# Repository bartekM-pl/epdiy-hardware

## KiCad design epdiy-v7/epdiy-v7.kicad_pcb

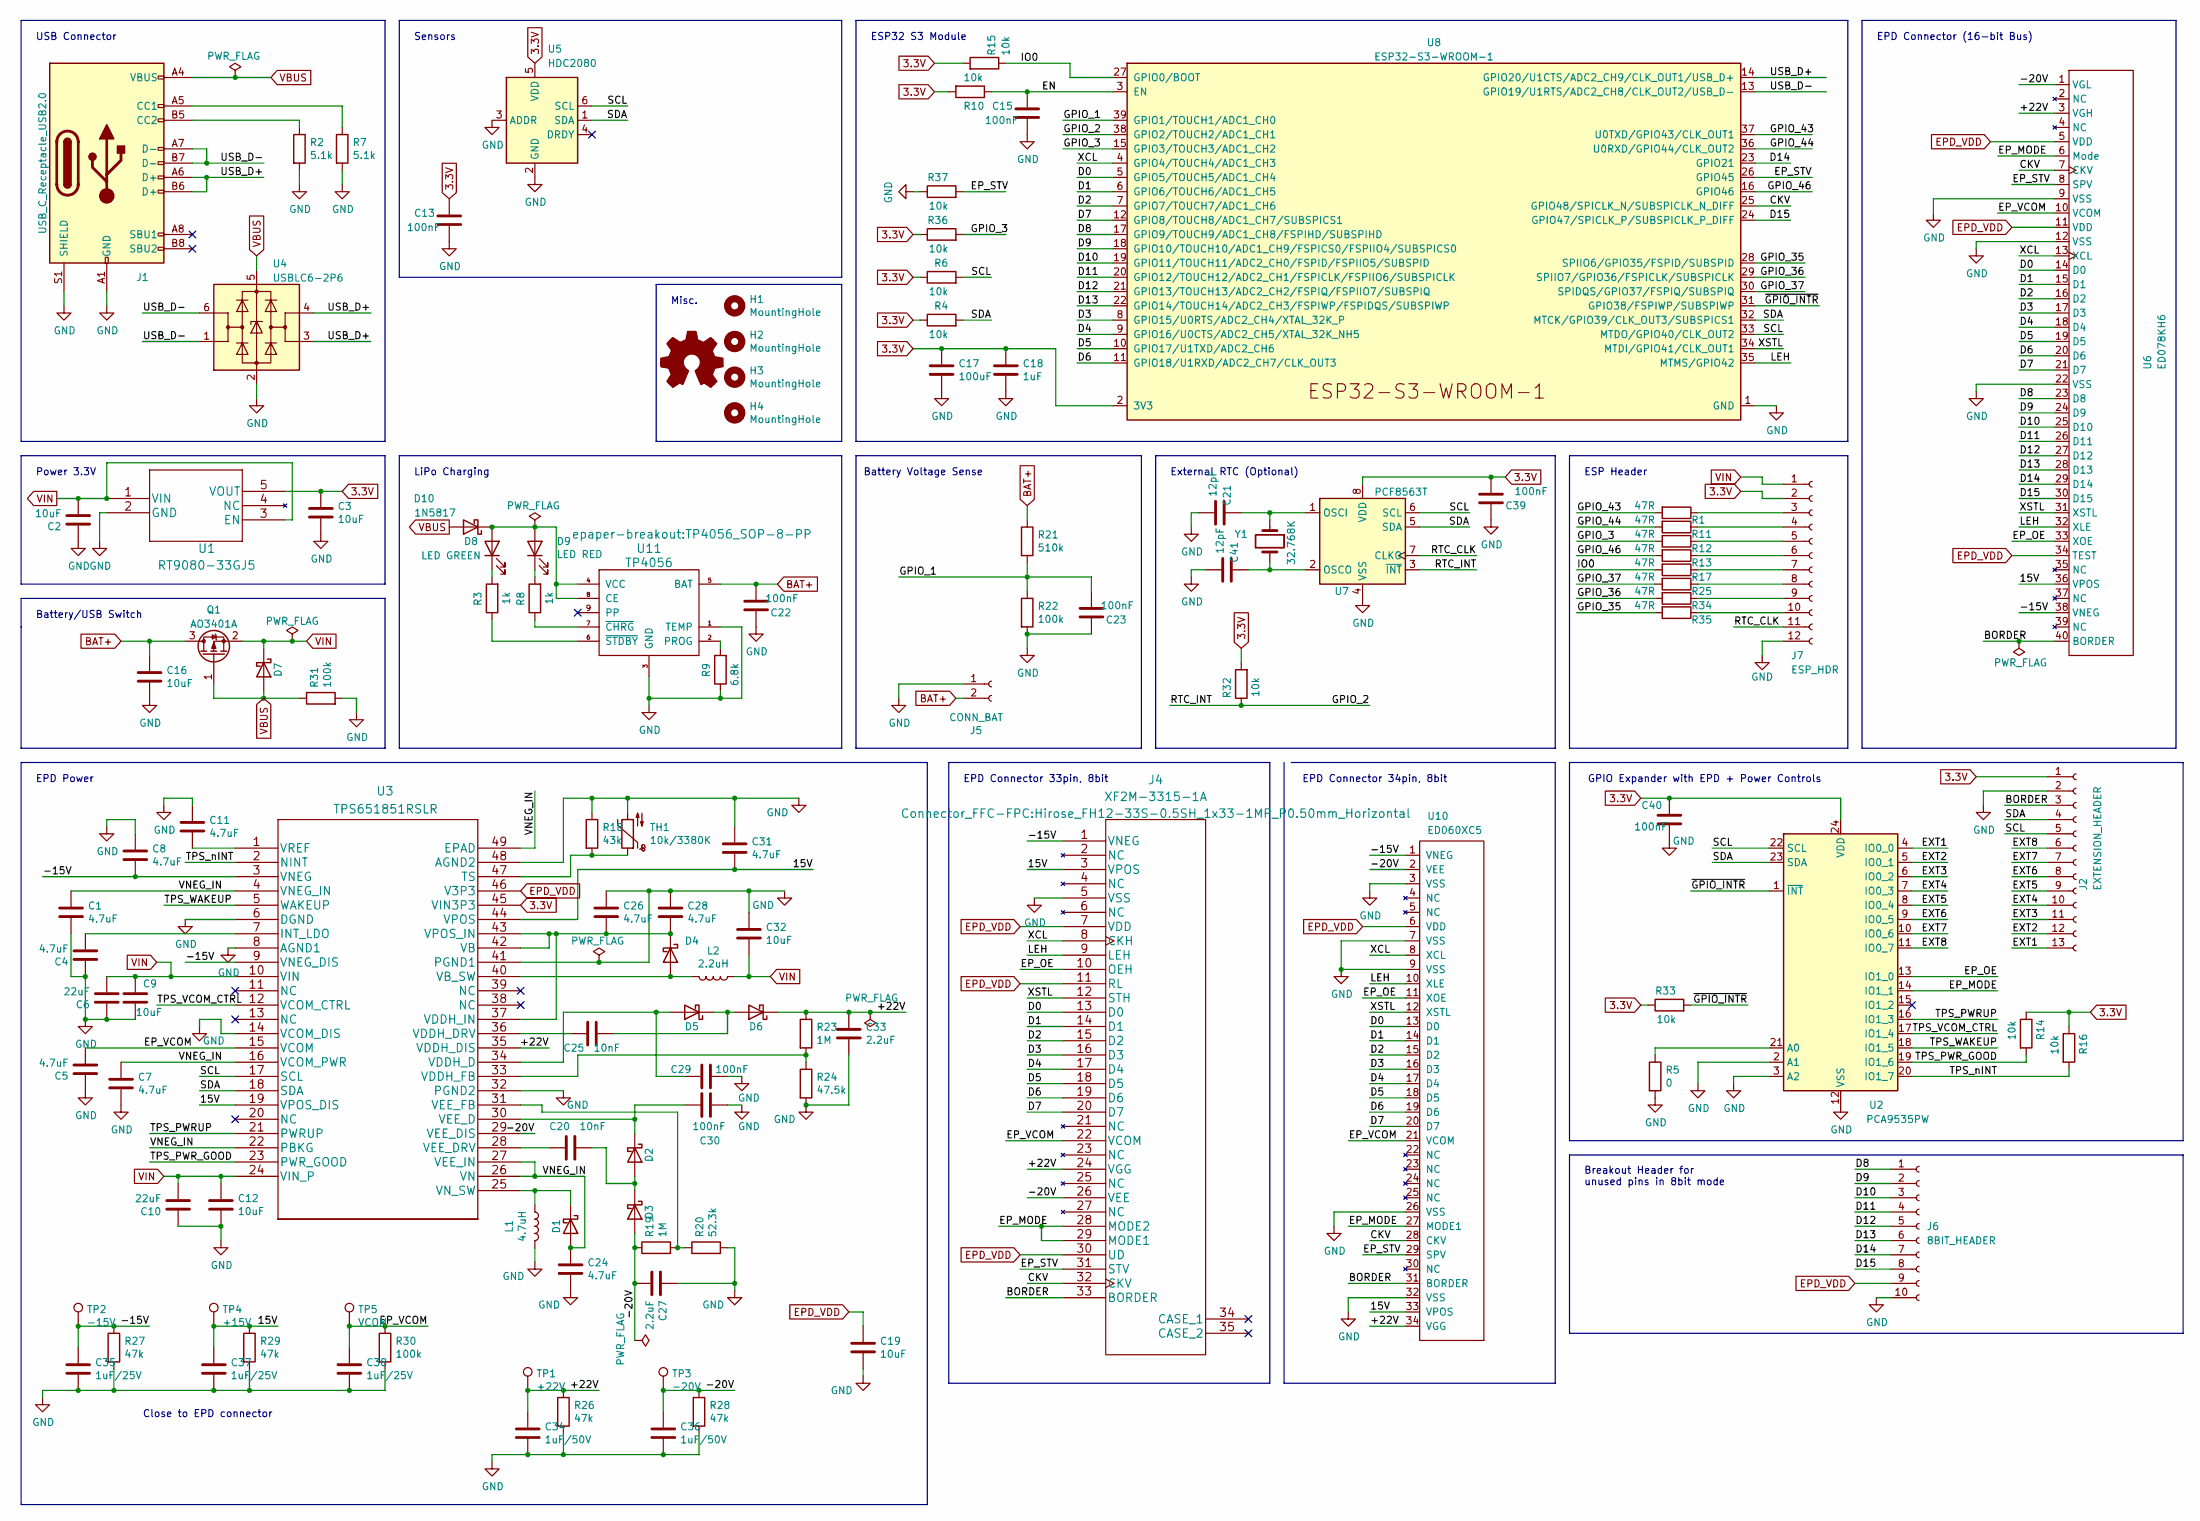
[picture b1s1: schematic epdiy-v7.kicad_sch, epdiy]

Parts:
C1, C4, C5, C7, C8, C11, C24, C26, C28, C31: 4.7uF; C_0805_2012Metric; LCSC C1779
C2, C3, C9, C12, C16, C19, C32: 10uF; C_0805_2012Metric; LCSC C15850
C6, C10: 22uF; C_0805_2012Metric; LCSC C45783
C13: 100nF; C_0603_1608Metric; LCSC C49678
C15, C22, C23, C29, C30, C39, C40: 100nF; C_0805_2012Metric; LCSC C49678
C17: 100uF; CP_EIA-3528-15_AVX-H; LCSC C16133
C18: 1uF; C_0805_2012Metric; LCSC C28323
C20, C25: 10nF; C_0805_2012Metric; LCSC C1710
C21, C41: 12pF; C_0603_1608Metric; LCSC C38523
C27, C33: 2.2uF; C_0805_2012Metric; LCSC C377773
C34, C36: 1uF/50V; C_1206_3216Metric; LCSC C1848
C35, C37, C38: 1uF/25V; C_0805_2012Metric; LCSC C28323
D1, D2, D3, D4, D5, D6, D7: MBR0540; D_SOD-123; LCSC C8598
D8: LED GREEN; LED_0603_1608Metric; LCSC C72043
D9: LED RED; LED_0603_1608Metric; LCSC C72038
D10: 1N5817; D_SOD-123; LCSC C8598
H1, H2, H3, H4: MountingHole; MountingHole_2.2mm_M2
J1: USB_C_Receptacle_USB2.0; USB_C_Receptacle_HRO_TYPE-C-31-M-12; LCSC C165948
J2: EXTENSION_HEADER; PinHeader_1x13_P2.54mm_Vertical
J4: XF2M-3315-1A; Hirose_FH12-33S-0.5SH_1x33-1MP_P0.50mm_Horizontal; LCSC C597986
J5: CONN_BAT; PinHeader_1x02_P2.54mm_Vertical
J6: 8BIT_HEADER; PinHeader_1x10_P2.54mm_Vertical
J7: ESP_HDR; PinHeader_1x12_P2.54mm_Vertical
L1: 4.7uH; L_Taiyo-Yuden_NR-50xx_HandSoldering; LCSC C222947
L2: 2.2uH; L_Taiyo-Yuden_NR-40xx_HandSoldering; LCSC C92959
Q1: AO3401A; SOT-23; LCSC C15127
R1, R11, R12, R13, R17, R25, R34, R35: 47R; R_0603_1608Metric; LCSC C25804
R2, R7: 5.1k; R_0603_1608Metric; LCSC C23186
R3, R8: 1k; R_0603_1608Metric; LCSC C21190
R4, R6, R10, R14, R15, R16, R32, R33, R36, R37: 10k; R_0603_1608Metric; LCSC C25804
R5: 0; R_0603_1608Metric; LCSC C21189
R9: 6.8k; R_0603_1608Metric; LCSC C23212
R18: 43k; R_0603_1608Metric; LCSC C23172
R19, R23: 1M; R_0603_1608Metric; LCSC C22935
R20: 52.3k; R_0603_1608Metric; LCSC C23196
R21: 510k; R_0603_1608Metric; LCSC C23192
R22: 100k; R_0603_1608Metric; LCSC C22807
R24: 47.5k; R_0603_1608Metric; LCSC C25819
R26, R27, R28, R29: 47k; R_0603_1608Metric; LCSC C25819
R30, R31: 100k; R_0603_1608Metric; LCSC C25803
TH1: 10k/3380K; R_0603_1608Metric; LCSC C76589
TP1: +22V; TestPoint_Pad_D2.5mm
TP2: -15V; TestPoint_Pad_D2.5mm
TP3: -20V; TestPoint_Pad_D2.5mm
TP4: +15V; TestPoint_Pad_D2.5mm
TP5: VCOM; TestPoint_Pad_D2.5mm
U1: RT9080-33GJ5; TSOT-23-5; LCSC C841192
U2: PCA9535PW; TSSOP-24_4.4x7.8mm_P0.65mm; LCSC C2652292
U3: TPS651851RSLR; LCSC C139292
U4: USBLC6-2P6; SOT-666; LCSC C2827693
U5: HDC2080; Texas_PWSON-N6; LCSC C918141
U6: ED078KH6; Hirose_FH12-40S-0.5SH_1x40-1MP_P0.50mm_Horizontal; LCSC C202114
U7: PCF8563T; SOIC-8_3.9x4.9mm_P1.27mm; LCSC C7440
U8: ESP32-S3-WROOM-1; LCSC C2913202
U10: ED060XC5; X05A20H34G; LCSC C528053
U11: TP4056; TP4056_SOP-8-PP; LCSC C16581
Y1: 32.768K; Crystal_SMD_3215-2Pin_3.2x1.5mm; LCSC C32346

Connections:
3.3V: C3.2, C13.1, C17.1, C18.2, C39.2, C40.1, J2.1, J7.2, R4.1, R6.1, R10.2, R14.1, R15.2, R16.1, R32.2, R33.1, R36.1, U1.5 (VOUT), U2.24 (VDD), U3.45 (VIN3P3), U5.5 (VDD), U7.8 (VDD), U8.2 (3V3)
/15V: C31.2, C37.1, J4.3 (VPOS), R29.1, TP4.1, U3.19 (VPOS_DIS), U3.44 (VPOS), U6.36 (VPOS), U10.33 (VPOS)
/+22V: C33.1, C34.1, D6.1 (K), J4.24 (VGG), R23.1, R26.1, TP1.1, U3.35 (VDDH_DIS), U6.3 (VGH), U10.34 (VGG)
/-15V: C8.2, C35.1, J4.1 (VNEG), R27.1, TP2.1, U3.3 (VNEG), U3.9 (VNEG_DIS), U6.38 (VNEG), U10.1 (VNEG)
/-20V: C27.2, C36.1, D3.2 (A), J4.26 (VEE), R19.1, R28.1, TP3.1, U3.29 (VEE_DIS), U6.1 (VGL), U10.2 (VEE)
/CKV: J4.32 (CKV), U6.7 (CKV), U8.25 (GPIO48/SPICLK_N/SUBSPICLK_N_DIFF), U10.28 (CKV)
/D0: J4.13 (D0), U6.14 (D0), U8.5 (GPIO5/TOUCH5/ADC1_CH4), U10.13 (D0)
/D1: J4.14 (D1), U6.15 (D1), U8.6 (GPIO6/TOUCH6/ADC1_CH5), U10.14 (D1)
/D2: J4.15 (D2), U6.16 (D2), U8.7 (GPIO7/TOUCH7/ADC1_CH6), U10.15 (D2)
/D3: J4.16 (D3), U6.17 (D3), U8.8 (GPIO15/U0RTS/ADC2_CH4/XTAL_32K_P), U10.16 (D3)
/D4: J4.17 (D4), U6.18 (D4), U8.9 (GPIO16/U0CTS/ADC2_CH5/XTAL_32K_NH5), U10.17 (D4)
/D5: J4.18 (D5), U6.19 (D5), U8.10 (GPIO17/U1TXD/ADC2_CH6), U10.18 (D5)
/D6: J4.19 (D6), U6.20 (D6), U8.11 (GPIO18/U1RXD/ADC2_CH7/CLK_OUT3), U10.19 (D6)
/D7: J4.20 (D7), U6.21 (D7), U8.12 (GPIO8/TOUCH8/ADC1_CH7/SUBSPICS1), U10.20 (D7)
/D8: J6.1, U6.23 (D8), U8.17 (GPIO9/TOUCH9/ADC1_CH8/FSPIHD/SUBSPIHD)
/D9: J6.2, U6.24 (D9), U8.18 (GPIO10/TOUCH10/ADC1_CH9/FSPICS0/FSPIIO4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)
/D10: J6.3, U6.25 (D10), U8.19 (GPIO11/TOUCH11/ADC2_CH0/FSPID/FSPIIO5/S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)
/D11: J6.4, U6.26 (D11), U8.20 (GPIO12/TOUCH12/ADC2_CH1/FSPICLK/FSPIIO6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)
/D12: J6.5, U6.27 (D12), U8.21 (GPIO13/TOUCH13/ADC2_CH2/FSPIQ/FSPIIO7/S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)
/D13: J6.6, U6.28 (D13), U8.22 (GPIO14/TOUCH14/ADC2_CH3/FSPIWP/FSPIDQS/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)
/D14: J6.7, U6.29 (D14), U8.23 (GPIO21)
/D15: J6.8, U6.30 (D15), U8.24 (GPIO47/SPICLK_P/SUBSPICLK_P_DIFF)
/EN: C15.1, R10.1, U8.3 (EN)
/EP_MODE: J4.28 (MODE2), J4.29 (MODE1), U2.14 (IO1_1), U6.6 (Mode), U10.27 (MODE1)
/EP_OE: J4.10 (OEH), U2.13 (IO1_0), U6.33 (XOE), U10.11 (XOE)
/EP_STV: J4.31 (STV), R37.2, U6.8 (SPV), U8.26 (GPIO45), U10.29 (SPV)
/EP_VCOM: C5.2, C38.1, J4.22 (VCOM), R30.1, TP5.1, U3.15 (VCOM), U6.10 (VCOM), U10.21 (VCOM)
/EXT1: J2.13, U2.4 (IO0_0)
/EXT2: J2.12, U2.5 (IO0_1)
/EXT3: J2.11, U2.6 (IO0_2)
/EXT4: J2.10, U2.7 (IO0_3)
/EXT5: J2.9, U2.8 (IO0_4)
/EXT6: J2.8, U2.9 (IO0_5)
/EXT7: J2.7, U2.10 (IO0_6)
/EXT8: J2.6, U2.11 (IO0_7)
/GPIO_1: C23.2, R21.2, R22.1, U8.39 (GPIO1/TOUCH1/ADC1_CH0)
/GPIO_2: R32.1, U7.3 (~INT), U8.38 (GPIO2/TOUCH2/ADC1_CH1)
/GPIO_3: R12.2, R36.2, U8.15 (GPIO3/TOUCH3/ADC1_CH2)
/GPIO_35: R35.2, U8.28 (SPIIO6/GPIO35/FSPID/SUBSPID)
/GPIO_36: R34.2, U8.29 (SPIIO7/GPIO36/FSPICLK/SUBSPICLK)
/GPIO_37: R25.2, U8.30 (SPIDQS/GPIO37/FSPIQ/SUBSPIQ)
/GPIO_43: R1.2, U8.37 (U0TXD/GPIO43/CLK_OUT1)
/GPIO_44: R11.2, U8.36 (U0RXD/GPIO44/CLK_OUT2)
/GPIO_46: R13.2, U8.16 (GPIO46)
/IO0: R15.1, R17.2, U8.27 (GPIO0/BOOT)
/LEH: J4.9 (LEH), U6.32 (XLE), U8.35 (MTMS/GPIO42), U10.10 (XLE)
/RTC_CLK: J7.11, U7.7 (CLKO)
/SCL: J2.5, R6.2, U2.22 (SCL), U3.17 (SCL), U5.6 (SCL), U7.6 (SCL), U8.33 (MTDO/GPIO40/CLK_OUT2)
/SDA: J2.4, R4.2, U2.23 (SDA), U3.18 (SDA), U5.1 (SDA), U7.5 (SDA), U8.32 (MTCK/GPIO39/CLK_OUT3/SUBSPICS1)
/TPS_PWRUP: U2.16 (IO1_3), U3.21 (PWRUP)
/TPS_PWR_GOOD: R14.2, U2.19 (IO1_6), U3.23 (PWR_GOOD)
/TPS_VCOM_CTRL: U2.17 (IO1_4), U3.12 (VCOM_CTRL)
/TPS_WAKEUP: U2.18 (IO1_5), U3.5 (WAKEUP)
/TPS_nINT: R16.2, U2.20 (IO1_7), U3.2 (NINT)
/USB_D+: J1.A6 (D+), J1.B6 (D+), U4.3 (I/O2), U4.4 (I/O2), U8.14 (GPIO20/U1CTS/ADC2_CH9/CLK_OUT1/USB_D+)
/USB_D-: J1.A7 (D-), J1.B7 (D-), U4.1 (I/O1), U4.6 (I/O1), U8.13 (GPIO19/U1RTS/ADC2_CH8/CLK_OUT2/USB_D-)
/VNEG_IN: C1.1, C7.1, C24.1, D1.2 (A), U3.4 (VNEG_IN), U3.16 (VCOM_PWR), U3.22 (PBKG), U3.26 (VN), U3.27 (VEE_IN), U3.49 (EPAD)
/XCL: J4.8 (CKH), U6.13 (XCL), U8.4 (GPIO4/TOUCH4/ADC1_CH3), U10.8 (XCL)
/XSTL: J4.12 (STH), U6.31 (XSTL), U8.34 (MTDI/GPIO41/CLK_OUT1), U10.12 (XSTL)
/~GPIO_INTR: R33.2, U2.1 (~INT), U8.31 (GPIO38/FSPIWP/SUBSPIWP)
BAT+: C16.2, C22.2, J5.2, Q1.3 (D), R21.1, U11.5 (BAT)
EPD_VDD: C19.1, J4.7 (VDD), J4.11 (RL), J4.30 (UD), J6.9, U3.46 (V3P3), U6.5 (VDD), U6.11 (VDD), U6.34 (TEST), U10.6 (VDD)
unnamed: D1.1 (K), L1.1, U3.25 (VN_SW)
unnamed: C20.1, D2.2 (A), D3.1 (K)
unnamed: C30.1, D2.1 (K), U3.30 (VEE_D)
unnamed: D4.2 (A), L2.2, U3.40 (VB_SW)
unnamed: C26.2, C28.2, D4.1 (K), U3.37 (VDDH_IN), U3.42 (VB), U3.43 (VPOS_IN)
unnamed: C29.2, D5.2 (A), U3.34 (VDDH_D)
unnamed: C25.1, D5.1 (K), D6.2 (A)
unnamed: D8.1 (K), R3.2
unnamed: D9.1 (K), R8.2
unnamed: D8.2 (A), D9.2 (A), D10.1 (K), U11.4 (VCC), U11.8 (CE)
unnamed: J1.A5 (CC1), R7.1
unnamed: J1.B5 (CC2), R2.1
unnamed: J7.3, R1.1
unnamed: J7.4, R11.1
unnamed: J7.5, R12.1
unnamed: J7.6, R13.1
unnamed: J7.7, R17.1
unnamed: J7.8, R25.1
unnamed: J7.9, R34.1
unnamed: J7.10, R35.1
unnamed: R5.1, U2.21 (A0)
unnamed: C4.2, U3.7 (INT_LDO)
unnamed: R18.2, TH1.1, U3.47 (TS)
unnamed: C25.2, U3.36 (VDDH_DRV)
unnamed: R23.2, R24.1, U3.33 (VDDH_FB)
unnamed: C20.2, U3.28 (VEE_DRV)
unnamed: R19.2, R20.1, U3.31 (VEE_FB)
unnamed: C11.2, U3.1 (VREF)
unnamed: C21.2, U7.1 (OSCI), Y1.1
unnamed: C41.2, U7.2 (OSCO), Y1.2
unnamed: R9.2, U11.2 (PROG)
unnamed: R8.1, U11.7 (~CHRG)
unnamed: R3.1, U11.6 (~STDBY)
VIN: C2.1, C6.2, C9.1, C10.2, C12.1, C32.2, D7.1 (K), J7.1, L2.1, Q1.2 (S), U1.1 (VIN), U1.3 (EN), U3.10 (VIN), U3.24 (VIN_P)

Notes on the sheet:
Battery Voltage Sense
Misc.
EPD Power
ESP Header
GPIO Expander with EPD + Power Controls
USB Connector
EPD Connector (16-bit Bus)
ESP32 S3 Module
Power 3.3V
EPD Connector 33pin, 8bit
Battery/USB Switch
External RTC (Optional)
EPD Connector 34pin, 8bit
Sensors
Breakout Header for unused pins in 8bit mode
LiPo Charging
Close to EPD connector

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
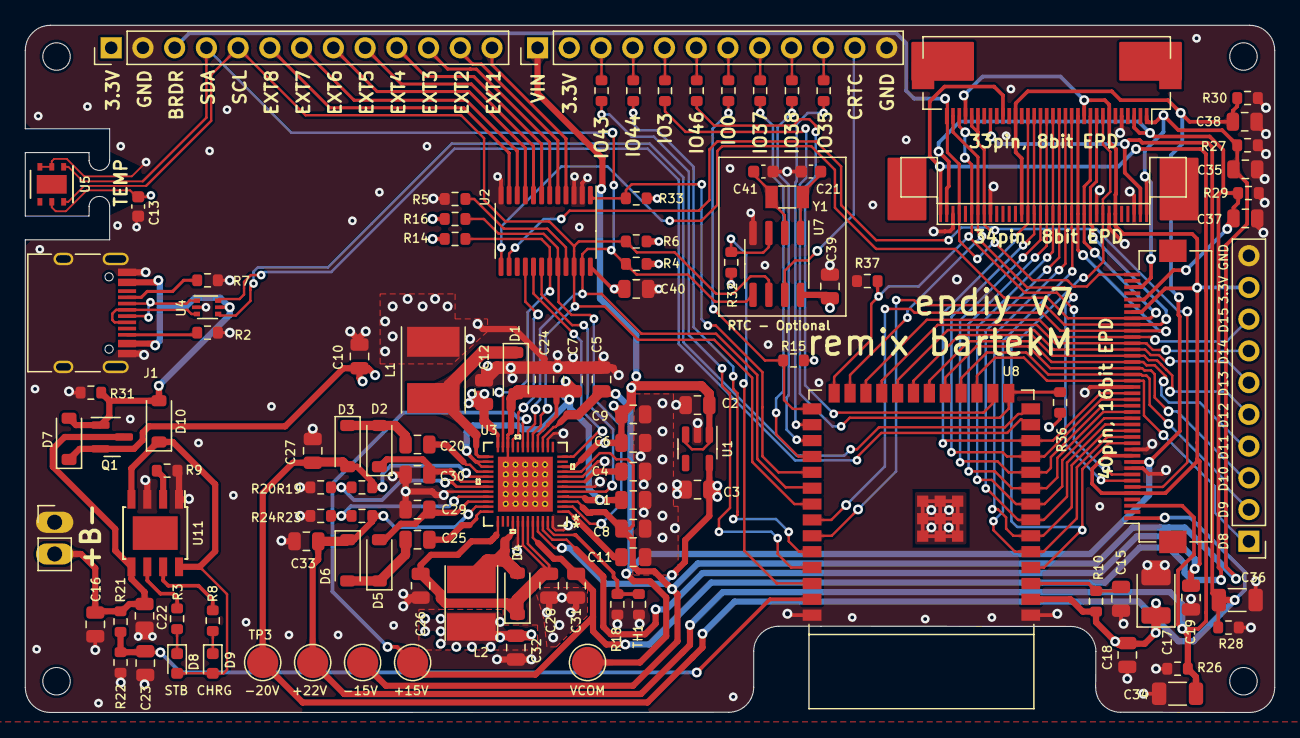
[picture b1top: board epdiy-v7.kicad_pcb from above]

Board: 4 copper layers, 100.0 x 55.0 mm, 117 parts (0 on the bottom side), 99 nets.

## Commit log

2024-01-09 Multiple changes. !!! Not for fabrication yet !!!
    -USB-UART bridge removed -programming with USB only
    -additional temperature and humidity sensor
    -PCB layout modified - more consistent traces width, more 0.7/0.3 vias, teardrops etc
    -jumpers removed and RX, TX signals routed to ext. pins

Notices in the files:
epdiy-v7/epdiy-v7.kicad_sch:
License: CC-BY-SA-4.0
parts and their libraries:
Copyright 2016 Accelerated Designs. All rights reserved.
